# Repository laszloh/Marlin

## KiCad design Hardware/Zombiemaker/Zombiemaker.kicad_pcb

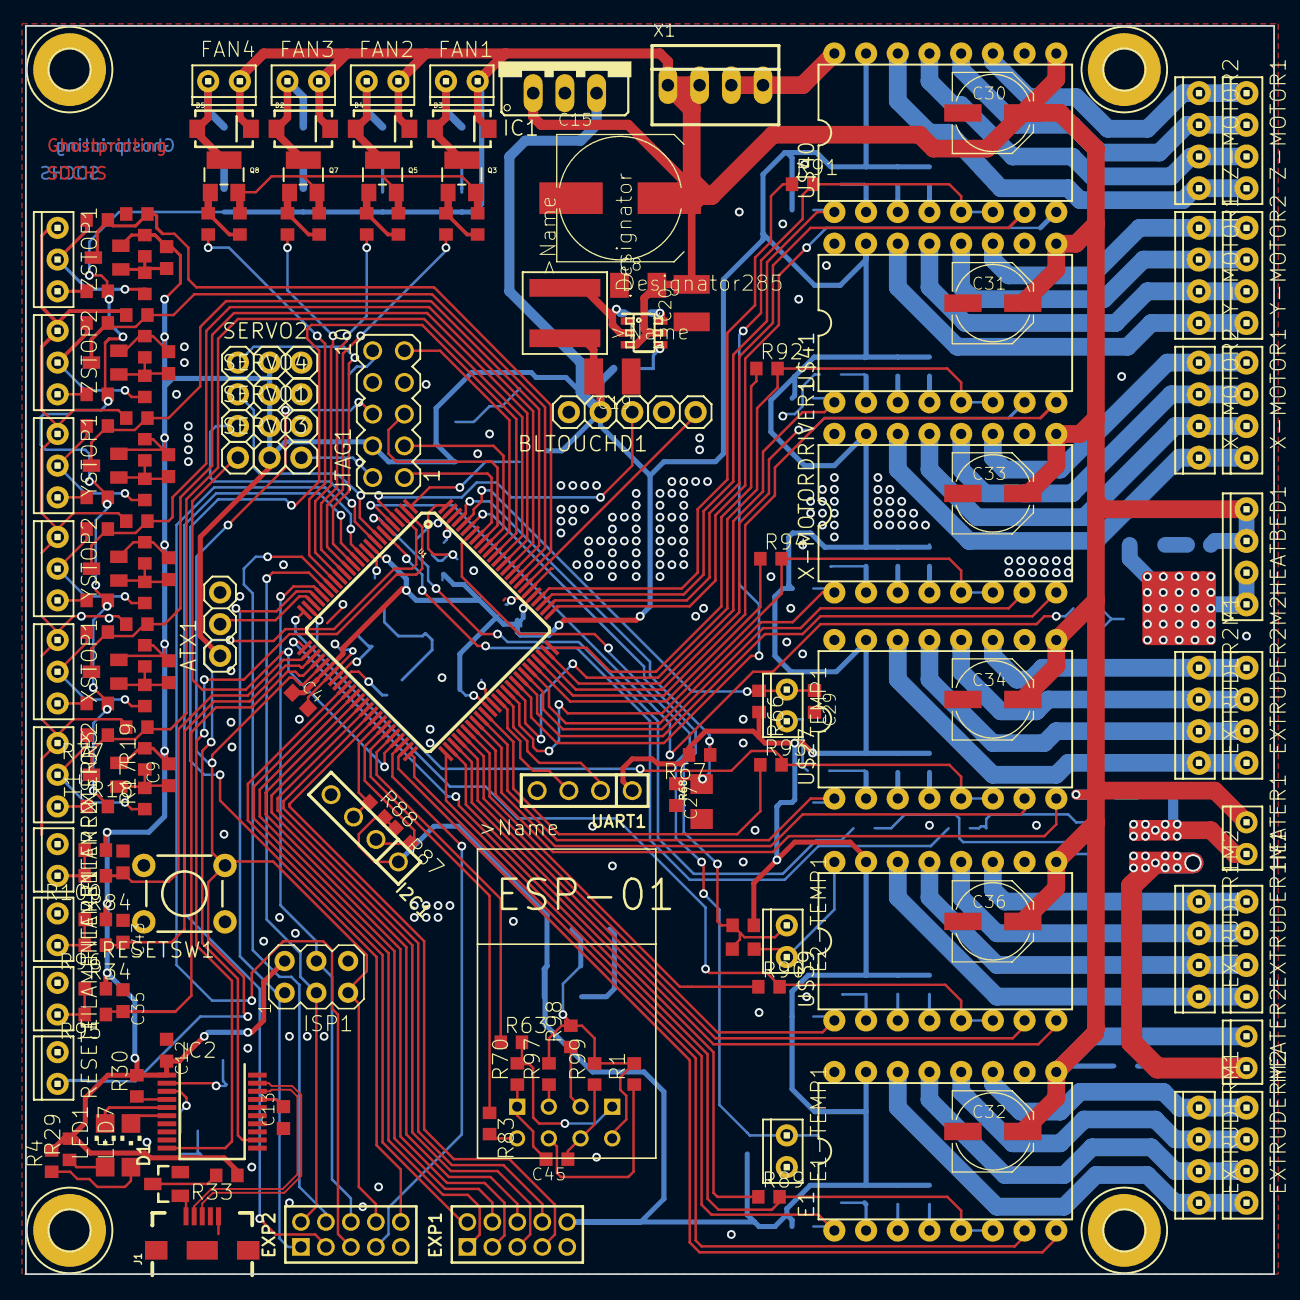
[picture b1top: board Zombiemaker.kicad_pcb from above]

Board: 2 copper layers, 100.0 x 100.0 mm, 254 parts (0 on the bottom side), 205 nets.

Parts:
ATX1: PINHD-1X3; 1X03
BLTOUCHD1: PINHD-1X3; 1X03
C1, C2, C14, C16: 22pF; C0603
C3, C4, C5, C6, C7, C22, C26, C27, C28, C29: C-EU_C0603K; C0603
C8, C39, C40: 100nF; C1206
C9, C10, C11, C12, C21, C23, C24, C25, C35, C37, C38, C43, C45, C46: 100nF; C0603
C13: 470nF; C0603
C15: ELKOS_UD-10X10; ELKO_SMDUD-10X10
C18: 100nF; C0805
C19: 47µF; C1210
C20: 22µF; C1210
C30, C31, C32, C33, C34, C36: 100µF; PANASONIC_D
D1: BAT54; SOT23
D2, D3, D4, D5: DIODE-SCHOTTKY_; SMA-DIODE
D6, D7: WS2812B
E1: POLOLUESTEPPERDRIVER; DIL16
E1-TEMP1, E2-TEMP1: MTA02-100; 10X02MTA
EXP1, EXP2: PINHD-2X5M; 2X05M
EXTRUDER1M1, EXTRUDER1M2, EXTRUDER2M1, EXTRUDER2M2: MTA04-100; 10X04MTA
EXTRUDERM1, EXTRUDERM2: MTA04-100; 10X04MTA
FAN1, FAN2, FAN3, FAN4: MTA02-100; 10X02MTA
FILAMENTERR1, FILAMENTERR2, FILAMENTERR3: MTA02-100; 10X02MTA
H1, H2, H3, H4: MOUNT-PAD-ROUND3.2; 3,2-PAD
HEATBED1: MTA04-100; 10X04MTA
HEATER1, HEATER2: MTA02-100; 10X02MTA
I2C1: MA04-1
IC1: 7805; 78XXS
IC2: MCP2200SSOP20; SSOP20
ISP1: AVRISP-6; AVRISP
J1: USB_MICRO-BREDUCED_PASTE; USB-B-MICRO-SMD_RED_PASTE
JP2: BLTOUCHS; 1X02
JP4, JP5, JP6, JP8, JP9, JP10, JP11, JP12, JP13, JP14, JP15, JP16, JP19, JP20, JP21, JP24, JP25, JP26: SJ
JTAG1: MA05-2
L1: XAL6030-332MEB; XAL6030
LED1, LED7: LEDS_CHIPLED_1206; CHIPLED_1206
LED2, LED3, LED4, LED5, LED6, LED9, LED10: LEDSMT1206; 1206
Q1: SI7960; POWERPAK-SO-08-DUAL
Q2: IRFR430; DPAK
Q3, Q5, Q7, Q8: MOSFET-NWAVE; SOT23-W
R1, R2, R3, R8, R11, R14, R34, R35, R36, R37, R38, R39, R56, R59, R62, R69, R71, R72, R73, R74, R75, R84, R89, R90, R91, R92, R93, R94, R95, R96, R97, R98, R99, R100, R101: 10k; R_SMD0603
R4, R29: 470; R_SMD0603
R5, R7, R10, R13, R16, R57, R60: 470; R_SMD0805
R6: 54.9k; R_SMD0603
R9: 10.2k; R_SMD0603
R12, R15, R18, R22, R26, R40, R41, R43, R45, R49, R53, R58, R61, R76, R77, R78, R79, R80, R81: 0; R_SMD0603
R17, R19, R21, R23, R25, R27, R44, R46, R48, R50, R52, R54: 1k; R_SMD0603
R20, R24, R28, R42, R47, R51, R55, R82: R-EU_R0603; R_SMD0603
R30, R31, R32, R33, R64, R65, R66, R67, R87, R88: 4k7; R_SMD0603
R63, R83: 1; R_SMD0603
R68: 6V/0.5A; 1206
R70: 2; R_SMD0603
RESET1: MTA02-100; 10X02MTA
RESETSW1: TAC_SWITCHPTH; TACTILE-PTH
SERVO1, SERVO2, SERVO3, SERVO4: PINHD-1X3; 1X03
T1, T2, T3, T4, T5, T6: -PNP-SOT23-BEC; SOT23-BEC
TEMP1: MTA02-100; 10X02MTA
U1: ATMEGA2560AU; TQFP100
U2: TPS565208DDCR; DDC0006A_N
U3: LM1117SOT223-WAVE; SOT223-W
U$3: ESP01
U$27, U$39, U$40, U$41: POLOLUESTEPPERDRIVER; DIL16
UART1: MA04-1
X1: 22-23-2041
X-MOTOR1, X-MOTOR2: MTA04-100; 10X04MTA
X-MOTORDRIVER1: POLOLUESTEPPERDRIVER; DIL16
XSTOP1, XSTOP2: MTA03-100; 10X03MTA
Y2, Y3: CRYSTALSMD-5X3.2-4PAD; CRYSTAL-SMD-5X3.2-4PAD
Y-MOTOR1, Y-MOTOR2: MTA04-100; 10X04MTA
YSTOP1, YSTOP2: MTA03-100; 10X03MTA
Z-MOTOR1, Z-MOTOR2: MTA04-100; 10X04MTA
ZSTOP1, ZSTOP2: MTA03-100; 10X03MTA

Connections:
+3V3: C39.2, R1.2, R97.2, R98.2, R99.2, U3.2, U$3.VCC
+5V: ATX1.1, BLTOUCHD1.2, C3.1, C4.1, C5.1, C6.1, C9.2, C10.2, C11.2, C12.2, C19.2, C23.2, C24.2, C25.2, C37.2, C38.2, C40.2, D6.1, D7.1, E1.10, EXP1.10, I2C1.1, IC1.OUT, IC2.1, ISP1.2, JP4.2, JP5.2, JP6.2, JP8.2, JP9.2, JP10.2, JP11.2, JP12.2, JP13.2, JP14.2, JP15.2, JP16.2, JP19.2, JP20.2, JP21.2, JP24.2, JP25.2, JP26.2, JTAG1.4, L1.2, R4.2, R6.2, R19.2, R23.2, R27.2, R29.2, R30.2, R31.2, R33.1, R34.2, R35.1, R36.1, R37.1, R38.1, R39.1, R42.2, R46.2, R50.2, R54.2, R62.1, R64.2, R65.2, R66.2, R67.2, R84.2, R87.2, R88.2, R101.2, SERVO1.2, SERVO2.2, SERVO3.2, SERVO4.2, T1.E, T2.E, T3.E, T4.E, T5.E, T6.E, U1.10, U1.31, U1.61, U1.80, U3.3, U$27.10, U$39.10, U$40.10, U$41.10, UART1.1, X-MOTORDRIVER1.10
+12V: C8.2, C15.P, C20.2, C30.P, C31.P, C32.P, C33.P, C34.P, C36.P, D2.C, D3.C, D4.C, D5.C, E1.16, FAN1.2, FAN2.2, FAN3.2, FAN4.2, HEATBED1.1, HEATBED1.2, HEATER1.1, HEATER2.1, IC1.IN, R5.2, R7.2, R10.2, R13.2, R16.2, R18.2, R22.2, R26.2, R45.2, R49.2, R53.2, R57.2, R60.2, U2.3, U2.5, U$27.16, U$39.16, U$40.16, U$41.16, X1.1, X1.2, X-MOTORDRIVER1.16
/Zombiemaker-1.0_2/BLTOUCH: BLTOUCHD1.1, U1.4
/Zombiemaker-1.0_2/DIS_01: EXP1.2, U1.35
/Zombiemaker-1.0_2/DIS_07: EXP1.1, U1.36
/Zombiemaker-1.0_2/DIS_08: EXP1.4, U1.37
/Zombiemaker-1.0_2/DIS_09: EXP1.3, U1.38
/Zombiemaker-1.0_2/DIS_10: EXP1.6, U1.39
/Zombiemaker-1.0_2/DIS_11: EXP1.5, U1.40
/Zombiemaker-1.0_2/DIS_12: EXP1.8, U1.41
/Zombiemaker-1.0_2/DIS_13: EXP1.7, U1.42
/Zombiemaker-1.0_2/FILAMENTERROR1: C35.2, R95.1, U1.29
/Zombiemaker-1.0_2/FILAMENTERROR2: C43.2, R96.1, U1.28
/Zombiemaker-1.0_2/FILAMENTERROR3: C46.2, R100.1, U1.27
/Zombiemaker-1.0_2/KILL: EXP2.10, U1.89
/Zombiemaker-1.0_2/MISO: EXP2.1, ISP1.1, U1.22
/Zombiemaker-1.0_2/MOSI: EXP2.6, ISP1.4, U1.21
/Zombiemaker-1.0_2/PS_ON: ATX1.2, U1.23
/Zombiemaker-1.0_2/RESET: C18.1, EXP2.8, ISP1.5, JTAG1.6, R31.1, RESET1.2, RESETSW1.3, U1.30
/Zombiemaker-1.0_2/RESET_3V3: C45.1, R99.1, U$3.RST
/Zombiemaker-1.0_2/RXD1: R83.1, U1.45
/Zombiemaker-1.0_2/RXD3: U1.63, UART1.3
/Zombiemaker-1.0_2/RXUSB: IC2.10, U1.2
/Zombiemaker-1.0_2/S-E1: EXP2.5, U1.12
/Zombiemaker-1.0_2/S-E2: EXP2.3, U1.13
/Zombiemaker-1.0_2/SCK: EXP2.2, ISP1.3, U1.20
/Zombiemaker-1.0_2/SCL: I2C1.3, R88.1, U1.43
/Zombiemaker-1.0_2/SDA: I2C1.2, R87.1, U1.44
/Zombiemaker-1.0_2/SD_CARD: EXP2.7, U1.48
/Zombiemaker-1.0_2/SERVO1: SERVO4.1, U1.8
/Zombiemaker-1.0_2/SERVO2: SERVO1.1, U1.9
/Zombiemaker-1.0_2/SERVO3: SERVO2.1, U1.14
/Zombiemaker-1.0_2/SERVO4: SERVO3.1, U1.47
/Zombiemaker-1.0_2/SS: EXP2.4, U1.19
/Zombiemaker-1.0_2/STATUSLED: D6.4, U1.1
/Zombiemaker-1.0_2/TCK: JTAG1.1, U1.93
/Zombiemaker-1.0_2/TDI: JTAG1.9, U1.90
/Zombiemaker-1.0_2/TDO: JTAG1.3, U1.91
/Zombiemaker-1.0_2/TMS: JTAG1.5, U1.92
/Zombiemaker-1.0_2/TXD1: R63.1, U1.46
/Zombiemaker-1.0_2/TXD3: U1.64, UART1.2
/Zombiemaker-1.0_2/TXUSB: IC2.12, U1.3
/Zombiemaker-1.0_2/ZMIN: JP2.1, U1.82
DIR_E: E1.8, U1.49
DIR_E1: U1.53, U$39.8
DIR_E2: U1.57, U$27.8
DIR_X: U1.68, X-MOTORDRIVER1.8
DIR_Y: U1.72, U$41.8
DIR_Z: U1.76, U$40.8
EN_E: E1.1, R62.2, U1.51
EN_E1: R35.2, U1.55, U$39.1
EN_E2: R39.2, U1.59, U$27.1
EN_X: R38.2, U1.70, X-MOTORDRIVER1.1
EN_Y: R37.2, U1.74, U$41.1
EN_Z: R36.2, U1.78, U$40.1
FAN1: R41.2, U1.15
FAN2: R12.2, U1.16
FAN3: R58.2, U1.17
FAN4: R61.2, U1.18
GND: ATX1.3, BLTOUCHD1.3, C1.2, C2.2, C3.2, C4.2, C5.2, C6.2, C8.1, C12.1, C13.1, C14.2, C15.M, C16.2, C18.2, C19.1, C20.1, C26.2, C27.2, C28.2, C29.2, C30.M, C31.M, C32.M, C33.M, C34.M, C35.1, C36.M, C37.1, C38.1, C43.1, C45.2, C46.1, D6.3, D7.3, E1.9, E1.15, E1-TEMP1.2, E2-TEMP1.2, EXP1.9, EXP2.9, FILAMENTERR1.1, FILAMENTERR2.1, FILAMENTERR3.1, H1.B3,2, H2.B3,2, H3.B3,2, H4.B3,2, I2C1.4, IC1.GND, IC2.20, ISP1.6, J1.GND, J1.SHIELD1, J1.SHIELD2, J1.SHIELD3, JP2.2, JTAG1.2, JTAG1.10, Q1.1, Q1.3, Q2.3, Q3.2, Q5.2, Q7.2, Q8.2, R2.1, R3.1, R8.1, R9.1, R11.1, R14.1, R20.1, R24.1, R28.1, R47.1, R51.1, R55.1, R56.1, R59.1, R68.1, R69.2, R70.1, R71.2, R72.2, R73.2, R74.2, R75.2, RESET1.1, RESETSW1.1, SERVO1.3, SERVO2.3, SERVO3.3, SERVO4.3, TEMP1.2, U1.11, U1.32, U1.62, U1.81, U2.1, U$3.GND, U$27.9, U$27.15, U$39.9, U$39.15, U$40.9, U$40.15, U$41.9, U$41.15, UART1.4, X1.3, X1.4, X-MOTORDRIVER1.9, X-MOTORDRIVER1.15, XSTOP1.1, XSTOP2.1, YSTOP1.1, YSTOP2.1, ZSTOP1.1, ZSTOP2.1
HEATBED: R15.2, U1.5
HEATER1: R43.2, U1.7
HEATER2: R40.2, U1.6
unnamed: C14.1, R32.2, Y2.3
unnamed: C1.1, U1.33, Y3.3
unnamed: C2.1, R82.2, Y3.1
unnamed: C7.2, U1.98
unnamed: C9.1, R17.2, R19.1, T1.B
unnamed: C10.1, R21.2, R23.1, T2.B
unnamed: C11.1, R25.2, R27.1, T3.B
unnamed: C13.2, IC2.17
unnamed: C16.1, IC2.2, Y2.1
unnamed: C21.1, L1.1, U2.2
unnamed: C21.2, U2.6
unnamed: C7.1, C22.1, U1.99
unnamed: C22.2, R42.1, U1.100
unnamed: C23.1, R44.2, R46.1, T4.B
unnamed: C24.1, R48.2, R50.1, T5.B
unnamed: C25.1, R52.2, R54.1, T6.B
unnamed: C39.1, C40.1, U3.1
unnamed: D1.1, J1.VBUS
unnamed: D1.3, R33.2
unnamed: D2.A, FAN3.1, LED9.C, Q7.3
unnamed: D3.A, FAN1.1, LED4.C, Q3.3
unnamed: D4.A, FAN2.1, LED6.C, Q5.3
unnamed: D5.A, FAN4.1, LED10.C, Q8.3
unnamed: D6.2, D7.4
unnamed: E1.2, JP13.1, R69.1
unnamed: E1.3, JP12.1
unnamed: E1.4, JP8.1
unnamed: E1.11, EXTRUDERM1.4, EXTRUDERM2.4
unnamed: E1.12, EXTRUDERM1.3, EXTRUDERM2.3
unnamed: E1.13, EXTRUDERM1.2, EXTRUDERM2.2
unnamed: E1.14, EXTRUDERM1.1, EXTRUDERM2.1
unnamed: EXTRUDER1M1.1, EXTRUDER1M2.1, U$39.14
unnamed: EXTRUDER1M1.2, EXTRUDER1M2.2, U$39.13
unnamed: EXTRUDER1M1.3, EXTRUDER1M2.3, U$39.12
unnamed: EXTRUDER1M1.4, EXTRUDER1M2.4, U$39.11
unnamed: EXTRUDER2M1.1, EXTRUDER2M2.1, U$27.14
unnamed: EXTRUDER2M1.2, EXTRUDER2M2.2, U$27.13
unnamed: EXTRUDER2M1.3, EXTRUDER2M2.3, U$27.12
unnamed: EXTRUDER2M1.4, EXTRUDER2M2.4, U$27.11
unnamed: FILAMENTERR1.2, R34.1, R95.2
unnamed: FILAMENTERR2.2, R84.1, R96.2
unnamed: FILAMENTERR3.2, R100.2, R101.1
unnamed: HEATBED1.3, HEATBED1.4, LED5.C, Q2.2
unnamed: HEATER1.2, LED3.C, Q1.5-6
unnamed: HEATER2.2, LED2.C, Q1.7-8
unnamed: IC2.3, R32.1
unnamed: IC2.4, R30.1
unnamed: IC2.5, LED1.C
unnamed: IC2.6, LED7.C
unnamed: IC2.18, J1.D-
unnamed: IC2.19, J1.D+
unnamed: JP4.1, U$27.4
unnamed: JP5.1, U$27.3
unnamed: JP6.1, R71.1, U$27.2
unnamed: JP9.1, U$39.4
unnamed: JP10.1, U$39.3
unnamed: JP11.1, R72.1, U$39.2
unnamed: JP14.1, U$40.4
unnamed: JP15.1, U$40.3
unnamed: JP16.1, R73.1, U$40.2
unnamed: JP19.1, U$41.4
unnamed: JP20.1, U$41.3
unnamed: JP21.1, R74.1, U$41.2
unnamed: JP24.1, X-MOTORDRIVER1.4
unnamed: JP25.1, X-MOTORDRIVER1.3
unnamed: JP26.1, R75.1, X-MOTORDRIVER1.2
unnamed: LED1.A, R29.1
unnamed: LED2.A, R5.1
unnamed: LED3.A, R7.1
unnamed: LED4.A, R10.1
unnamed: LED5.A, R13.1
unnamed: LED6.A, R16.1
unnamed: LED7.A, R4.1
unnamed: LED9.A, R57.1
unnamed: LED10.A, R60.1
unnamed: Q1.2, R2.2, R40.1
unnamed: Q1.4, R3.2, R43.1
unnamed: Q2.1, R11.2, R15.1
unnamed: Q3.1, R8.2, R41.1
unnamed: Q5.1, R12.1, R14.2
unnamed: Q7.1, R56.2, R58.1
unnamed: Q8.1, R59.2, R61.1
unnamed: R1.1, U$3.CH_PD
unnamed: R6.1, R9.2, U2.4
unnamed: R17.1, R77.2, XSTOP2.2
unnamed: R18.1, XSTOP2.3
unnamed: R21.1, R79.2, YSTOP2.2
unnamed: R22.1, YSTOP2.3
unnamed: R25.1, R81.2, ZSTOP2.2
unnamed: R26.1, ZSTOP2.3
unnamed: R44.1, R76.2, XSTOP1.2
unnamed: R45.1, XSTOP1.3
unnamed: R48.1, R78.2, YSTOP1.2
unnamed: R49.1, YSTOP1.3
unnamed: R52.1, R80.2, ZSTOP1.2
unnamed: R53.1, ZSTOP1.3
unnamed: R63.2, R70.2, U$3.RX
unnamed: R82.1, U1.34
unnamed: R83.2, U$3.TX
unnamed: R97.1, U$3.GPIO2
unnamed: R98.1, U$3.GPIO0
unnamed: U$40.11, Z-MOTOR1.4, Z-MOTOR2.4
unnamed: U$40.12, Z-MOTOR1.3, Z-MOTOR2.3
unnamed: U$40.13, Z-MOTOR1.2, Z-MOTOR2.2
unnamed: U$40.14, Z-MOTOR1.1, Z-MOTOR2.1
unnamed: U$41.11, Y-MOTOR1.4, Y-MOTOR2.4
unnamed: U$41.12, Y-MOTOR1.3, Y-MOTOR2.3
unnamed: U$41.13, Y-MOTOR1.2, Y-MOTOR2.2
unnamed: U$41.14, Y-MOTOR1.1, Y-MOTOR2.1
unnamed: X-MOTOR1.1, X-MOTOR2.1, X-MOTORDRIVER1.14
unnamed: X-MOTOR1.2, X-MOTOR2.2, X-MOTORDRIVER1.13
unnamed: X-MOTOR1.3, X-MOTOR2.3, X-MOTORDRIVER1.12
unnamed: X-MOTOR1.4, X-MOTOR2.4, X-MOTORDRIVER1.11
RXE: E1.5, E1.6, R89.2, U1.26
RXE1: R90.2, U1.25, U$39.5, U$39.6
RXE2: R93.2, U1.24, U$27.5, U$27.6
RXX: R94.2, U1.65, X-MOTORDRIVER1.5, X-MOTORDRIVER1.6
RXY: R92.2, U1.66, U$41.5, U$41.6
RXZ: R91.2, U1.67, U$40.5, U$40.6
STEP_E: E1.7, U1.50
STEP_E1: U1.54, U$39.7
STEP_E2: U1.58, U$27.7
STEP_X: U1.69, X-MOTORDRIVER1.7
STEP_Y: U1.73, U$41.7
STEP_Z: U1.77, U$40.7
THERM1: C26.1, E1-TEMP1.1, R64.1, U1.94
THERM2: C28.1, E2-TEMP1.1, R65.1, U1.95
THERM3: C29.1, R66.1, TEMP1.1, U1.96
THERM_BOARD: C27.1, R67.1, R68.2, U1.97
TXE: R89.1, U1.52
TXE1: R90.1, U1.56
TXE2: R93.1, U1.60
TXX: R94.1, U1.71
TXY: R92.1, U1.75
TXZ: R91.1, U1.79
XSTOP: R20.2, R77.1, T1.C, U1.88
XSTOP1: R47.2, R76.1, T4.C, U1.87
YSTOP: R24.2, R79.1, T2.C, U1.86
YSTOP1: R51.2, R78.1, T5.C, U1.85
ZSTOP: R28.2, R81.1, T3.C, U1.84
ZSTOP1: R55.2, R80.1, T6.C, U1.83

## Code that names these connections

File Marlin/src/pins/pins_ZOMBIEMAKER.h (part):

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//
// Servos
//
#define SERVO0_PIN         78     // used for BLTOUCH
#define SERVO1_PIN         79
#define SERVO2_PIN         80
#define SERVO3_PIN         84
#define SERVO4_PIN         81

//
// Limit Switches
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#define HEATER_BED_PIN      3

#define FAN_PIN             6
#define FAN2_PIN            7
#define FAN3_PIN            8
#define FAN4_PIN            9

//
// Misc. Functions
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#define FIL2_RUNOUT_PIN    71
#define FIL3_RUNOUT_PIN    85

#define PS_ON_PIN          75

//////////////////////////
// LCDs and Controllers //
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
      #define BTN_ENC           35
      #define SD_DETECT_PIN     49
      #define KILL_PIN          41

      #if ENABLED(BQ_LCD_SMART_CONTROLLER)
        #define LCD_BACKLIGHT_PIN 39
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      #define BTN_EN2           43
      #define BTN_ENC           32
      #define LCD_SDSS          53
      #define KILL_PIN          41

    #elif ENABLED(LCD_I2C_VIKI)

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
      #define SDSS              53
      #define SD_DETECT_PIN     -1 // Pin 49 for display sd interface, 72 for easy adapter board
      #define KILL_PIN          31

    #elif ENABLED(ELB_FULL_GRAPHIC_CONTROLLER)

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
      #define LCD_SDSS          53
      #define SD_DETECT_PIN     82        // needs fixing
      #define KILL_PIN          41

    #elif ENABLED(MKS_MINI_12864)  // Added in Marlin 1.1.6

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
      #define SDSS              53
      #define SD_DETECT_PIN     49
      #define KILL_PIN          64

    #elif ENABLED(MINIPANEL)

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
      #define SDSS              53
      #define SD_DETECT_PIN     49
      #define KILL_PIN          64

    #elif ENABLED(ZONESTAR_LCD)

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
      #if ENABLED(G3D_PANEL)
        #define SD_DETECT_PIN   49
        #define KILL_PIN        41
      #endif

    #endif
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
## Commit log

2018-10-06 Zombiemaker board for the Marlin 2.0
2018-10-06 Finish the board specifiy files
    Not yet estes, but compiles well
2018-10-06 Enable all major parts of the board in the configuration
    Bugs found:
    -) SoftwareSerial and interrupt endstops are not supported at the same time
2018-10-06 Update configuration
    Configuration and pin update to the new namings of Marlin
2018-10-08 Add converted KiCAD files for the board
    Add KiCAD files for the Hardware
2018-10-08 WIP commit
    squash me after we are finished
2018-10-09 Update gitignore for KiCAD
    Update the .gitignore to include KiCAD backup & temprary files.
2018-10-09 WIP commit
    squash after finish
2018-10-09 Fix gitignore to not ignore KiCAD Libraries
2019-02-06 Configuration mods
    Modify the configuration to represent the 3D printer
2019-02-07 WIP commint
    Will have to be squashed and cleaned up.
2019-02-07 Make it compilable
2019-09-15 Add support for anycubic i3 mega
2019-09-24 Enable rotary filament runout detection
    Enable the runout detecttion through the rotary encoder and clean up the
    pins.h "mess".
2019-09-24 Modifying PID values to get a better thermal stability
    Due to the bad heaters, the PID in Marlin has a hard time with the
    Xeed printer.
2019-09-24 Makeing it run on the XEED
2019-09-24 Misc. configuration updates
2019-09-24 Add missing header
    For the M701/M702 command the features/pause.h must be present.
    Otherwise we have compile errors.
2019-09-24 Enable M701/M702 commands
    Enable the filament load and unload commands. Modify max extrusion
    lenght to allow for this.
2019-09-24 Fix G34 positions
2019-09-24 Move the head away for the end stops after homing
2019-09-24 Enable UBL insteal of Bilinear Bed leveling
2019-09-24 Update all files to the new marlin configuration
2019-09-24 Add a workspace and start modifying the pid
    again
2019-09-24 iConfiguration update for PID debugging
2019-09-24 temperature testing
2019-09-24 Change temperature residance time
2019-09-24 :Add support for the FANs
2019-10-02 mend
2019-10-11 Reenable Bed heater and fix G34
    Reenable the bed heater and fix the Z-stepper assignment for G34
2021-01-03 Add serial and anycubic TFT
    Add the 1.1.x files of the serial and the lcd display from here:
    https://github.com/derhopp/Marlin-with-Anycubic-i3-Mega-TFT
2021-01-03 Adapt the AnycubicTFT to Marlin 2.0
    Added the hooks from the TFT to the right places in Marlin 2.0.
    Also started to modify the behavior of the LCD code to better match
    my behavior taste.
    Some code still duplicates basic function of Marlin (f.e. checking
    for too high or too low temperature). This logic should be moved to
    the correspondig module (and we will then only be a consumer of the
2021-01-03 Initial Configuration for my printer
    With this config my (albeit modded) anycubic i3 mega is just printig
    fine.
2021-01-03 Add modified configuration
2021-01-03 Remove LCD parts
2021-01-03 Compile fix after rebase
2021-01-03 Make Marlin compile again
2021-01-09 Disbale Fast PWM for radial fan
2021-01-09 Enable second stepper driver
2021-01-09 fixes
2021-01-11 Set correct thermistor and fix pin definitions
2021-01-23 Add missing chipselect for SD card
2021-01-23 Change configuration to fit the classic extruder
2021-01-28 Add BLTOUCH support
2021-01-28 Enable propper caselight
2021-01-28 Fix wrong config
2021-01-29 Add missing ExtUI function
2021-01-31 fix case light bug and reenable it
2021-02-18 Have no uncommited changes
2021-02-18 Remove unneeded files since the 2015 leapfrog is now supported by Marlin
2021-02-18 Add missing SOL2 pin
2021-02-18 Modify the config to make the SW compilable

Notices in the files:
Marlin/src/pins/pins_ZOMBIEMAKER.h:
Copyright (C) 2016 MarlinFirmware [https://github.com/MarlinFirmware/Marlin]
Copyright (C) 2018 Laszlo Hegedüs / Stefan Sochovsky
This program is free software: you can redistribute it and/or modify
it under the terms of the GNU General Public License as published by
the Free Software Foundation, either version 3 of the License, or
(at your option) any later version.
